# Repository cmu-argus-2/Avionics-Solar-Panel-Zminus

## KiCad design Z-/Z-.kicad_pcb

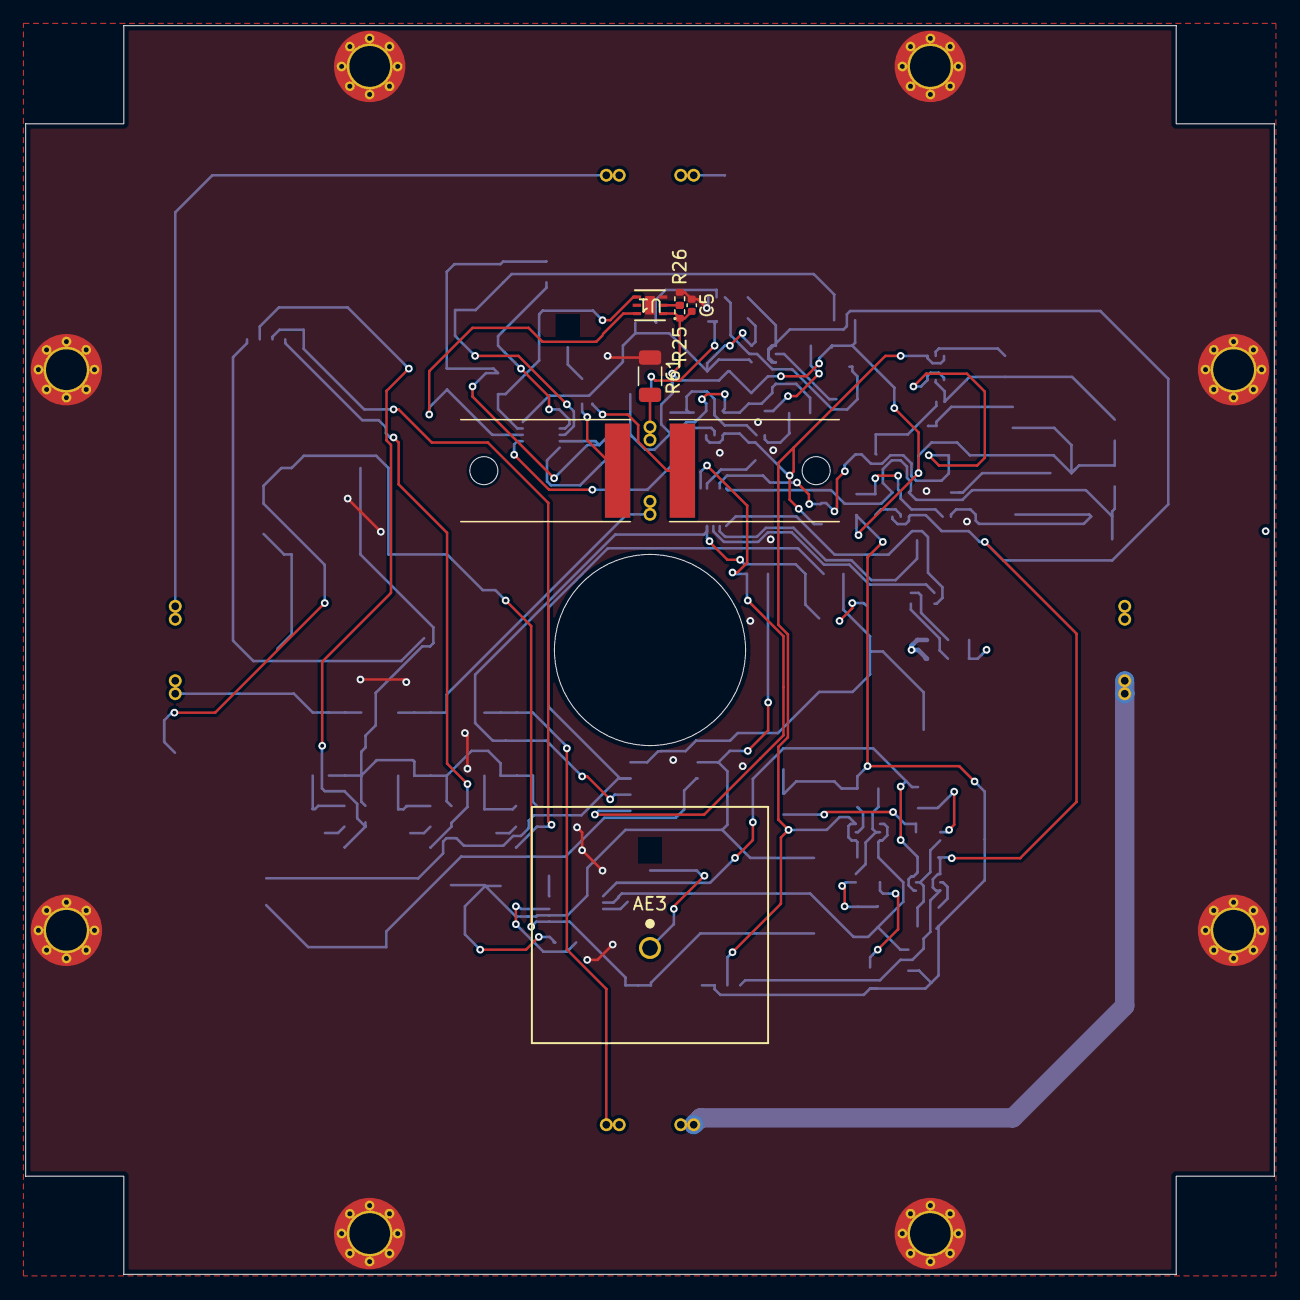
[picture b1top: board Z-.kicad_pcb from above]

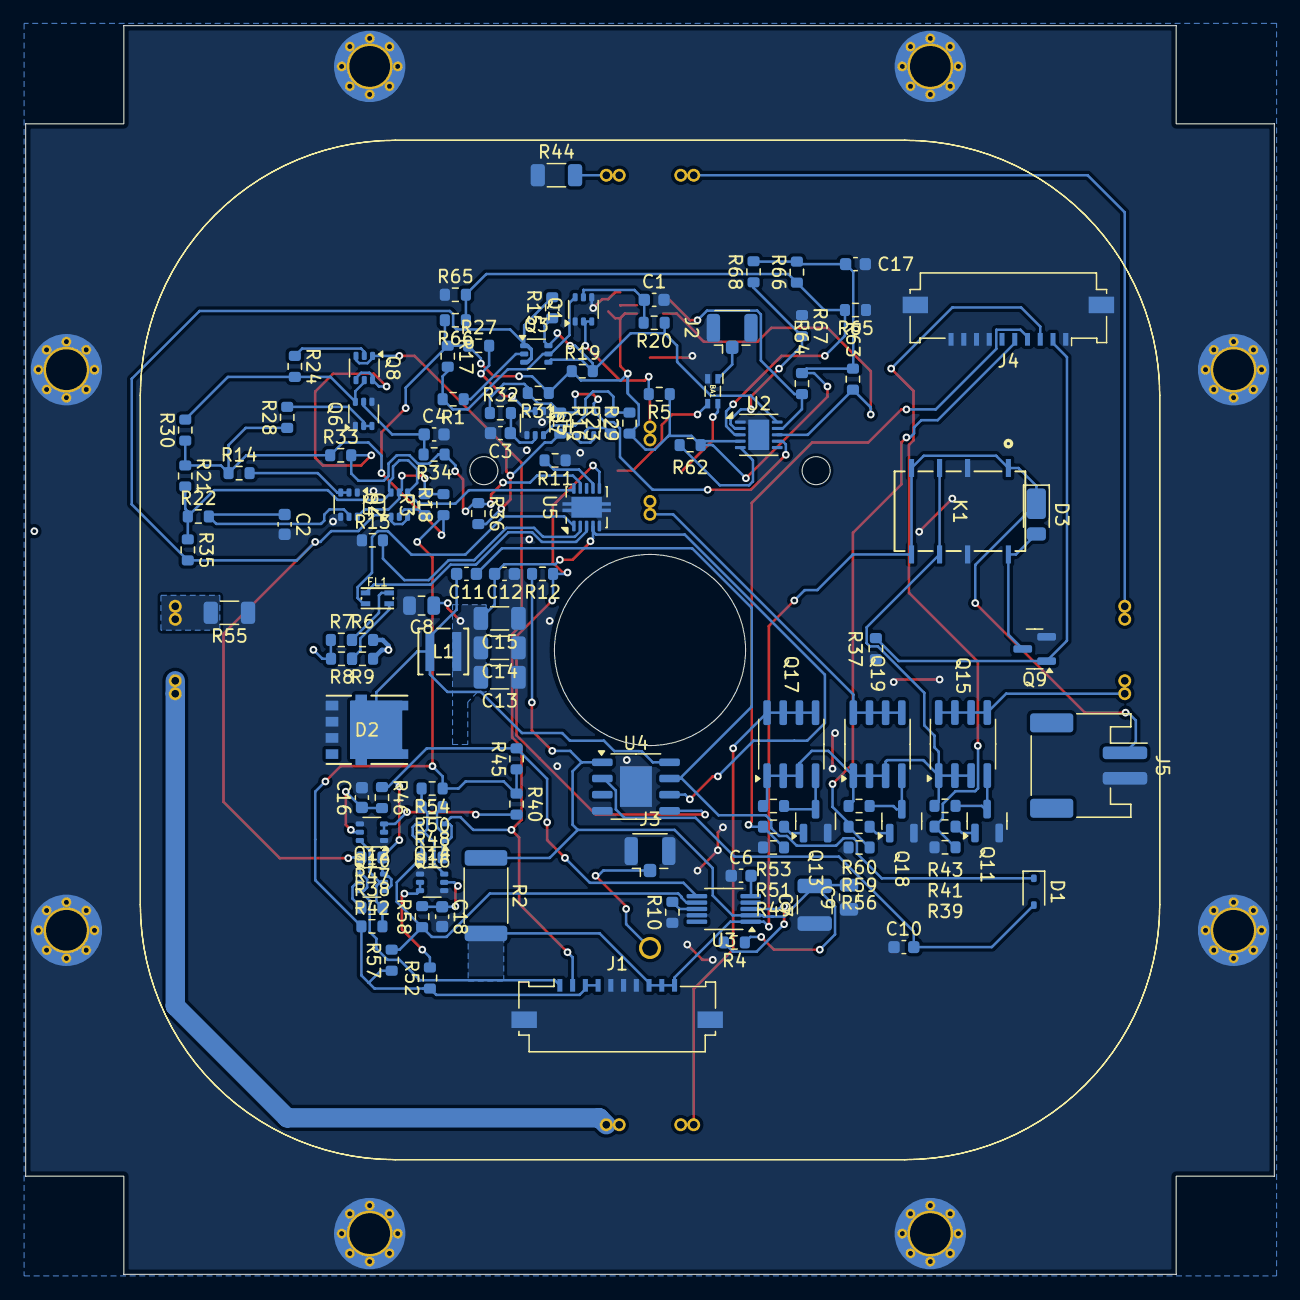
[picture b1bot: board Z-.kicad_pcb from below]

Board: 4 copper layers, 98.0 x 98.0 mm, 140 parts (121 on the bottom side), 81 nets.

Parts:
AE1, AE2: MountingHole_Pad; Antenna Mount
AE3: GPS Antenna; ANT_CGGBP.18.4.A.02_TAL
BA1: ATB2012-50011-T000; ATB2012
C1, C2, C3, C4, C16, C18: 10nF; C_0603_1608Metric
C5: 0.1uF; C_0402_1005Metric
C6: 3.3nF; C_0603_1608Metric
C7: 4.7uF; C_1210_3225Metric
C8: 0.1uF; C_0805_2012Metric
C9: 1uF; C_0805_2012Metric
C10, C11, C12, C17: 0.1uF; C_0603_1608Metric
C13, C14, C15: 10uF; C_1206_3216Metric
D1: BAS16HT1G; D_SOD-323
D2: NRVB440MFS; NRVB440MFSWFT1G
D3: DFLS130L; D_PowerDI-123
FL1: SRF2012
H1, H2, H3, H4, H5, H6, H7, H8: MountingHole_Pad; MountingHole_3.2mm_M3_DIN965_Pad_TopBottom
J1, J4: 200528-0100; Molex_200528-0100_1x10-1MP_P1.00mm_Horizontal
J2, J3: Conn_Coaxial; U.FL_Hirose_U.FL-R-SMT-1_Vertical
J5: Conn_01x02; JST_PH_S2B-PH-SM4-TB_1x02-1MP_P2.00mm_Horizontal
JP1, JP2, JP3, JP4, JP5: BurnWire; Burn-Wire
K1: IM02DGR; RELAY8_SMTGUL_TEC
L1: XGL3520-222; XGL3520
Q1, Q2, Q5, Q6, Q10, Q14: NX3008NBKS; SOT-363_SC-70-6
Q3, Q4, Q7, Q8, Q12, Q16: MBT2222ADW1T1; SOT-363_SC-70-6
Q9: MMBT2222AT; SOT-23
Q11, Q13, Q18: IRLML2803; SOT-23
Q15, Q17, Q19: IRF7404; SOIC-8_3.9x4.9mm_P1.27mm
R1, R3, R23, R24, R38, R50: 680R; R_0603_1608Metric
R2: ?R; R_2512_6332Metric
R4: 1K; R_0603_1608Metric
R5, R14, R27, R28, R40, R43, R52, R53, R60: 100K; R_0603_1608Metric
R6, R7, R8, R9, R10, R11, R13, R65#2: 0R; R_0603_1608Metric
R12, R17, R18, R19, R21, R29, R30, R31, R33, R37, R39, R42, R45, R49, R54, R56, R57, R62, R63, R64: 10K; R_0603_1608Metric
R15, R16, R35, R36, R47, R48, R66#2: DNI (0R); R_0603_1608Metric
R20, R22, R32, R34, R46, R58: 200K; R_0603_1608Metric
R25, R26: 0R; R_0402_1005Metric
R41, R51, R59: 4.7K; R_0603_1608Metric
R44, R55, R61: 1R; R_1206_3216Metric
R65, R66: ?; R_0603_1608Metric
R67: 102K; R_0603_1608Metric
R68: 976K; R_0603_1608Metric
U1: OPT4003DNPRQ1; OPT4003
U2: LTC4316xDD; DFN-10-1EP_3x3mm_P0.5mm_EP1.65x2.38mm
U3: ADM1176-1ARMZ-R7; MSOP-10_3x3mm_P0.5mm
U4: NCV891330PD50R2G; SOIC-8-1EP_3.9x4.9mm_P1.27mm_EP2.514x3.2mm
U5: DRV8830DRC; VSON-10-1EP_3x3mm_P0.5mm_EP1.65x2.4mm

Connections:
3.3V: C5.1, C17.1, J1.3, J1.4, R5.1, R14.1, R17.1, R18.1, R19.1, R21.1, R25.2, R27.1, R28.1, R29.1, R30.1, R31.1, R33.1, R40.1, R42.1, R45.1, R52.1, R54.1, R57.1, R62.2, R63.2, R64.2, R66.2, R66#2.2, R68.2, U1.1 (VDD), U2.4 (V_{CC})
+5V: C8.1, C12.2, C13.2, C14.2, C15.2, L1.2, U4.6 (VOUT), U5.4 (VCC)
/Burn Wires/VBURN1: JP1.1, Q15.5 (Drain), Q15.6 (Drain), Q15.7 (Drain), Q15.8 (Drain)
/Burn Wires/VBURN2: JP2.1, Q17.5 (Drain), Q17.6 (Drain), Q17.7 (Drain), Q17.8 (Drain)
/Burn Wires/VBURN3: JP3.1, Q19.5 (Drain), Q19.6 (Drain), Q19.7 (Drain), Q19.8 (Drain)
/Burn Wires/VBURN_A_IN: K1.3, K1.6, Q15.1 (Source), Q15.2 (Source), Q15.3 (Source), Q17.1 (Source), Q17.2 (Source), Q17.3 (Source), Q19.1 (Source), Q19.2 (Source), Q19.3 (Source), R43.2, R53.2, R60.2
/I2C Devices/SCLOUT: R64.1, U1.4 (SCL), U2.9 (SCLOUT)
/I2C Devices/SDAOUT: R63.1, U1.6 (SDA), U2.8 (SDAOUT)
/coil: R6.2, R7.1, R8.2, R9.1
BURN_EN1: J4.3, R39.1, R41.2
BURN_EN2: J4.4, R49.1, R51.2
BURN_EN3: J4.5, R56.1, R59.2
BURN_RELAY_A: J4.2, Q9.1 (B), R37.1
COIL_N: FL1.4, R8.1, R9.2
COIL_P: FL1.2, R6.1, R7.2
GND: BA1.2 (GND), C1.2, C2.2, C3.2, C4.2, C5.2, C6.1, C7.1, C8.2, C9.1, C10.1, C12.1, C13.1, C14.1, C15.1, C16.2, C17.2, C18.2, D2.2 (A), H1.1, H2.1, H3.1, H4.1, H5.1, H6.1, H7.1, H8.1, J1.5, J1.6, J1.7, J1.MP (MountPin), J2.2 (Ext), J3.2 (Ext), J4.1, J4.7, J4.8, J4.9, J4.10, J4.MP (MountPin), J5.2, K1.2, K1.7, Q1.1 (S2), Q1.4 (S1), Q2.1 (S2), Q2.4 (S1), Q5.1 (S2), Q5.4 (S1), Q6.1 (S2), Q6.4 (S1), Q9.2 (E), Q10.1 (S2), Q10.4 (S1), Q11.2 (S), Q13.2 (S), Q14.1 (S2), Q14.4 (S1), Q18.2 (S), R10.1, R11.1, R13.1, R26.1, R37.2, R39.2, R44.1, R49.2, R55.1, R56.2, R61.1, R65.1, R65#2.1, R67.1, U1.3 (GND), U1.7 (EPAD), U2.1 (GND), U2.11 (EP), U3.4 (GND), U3.9 (A1), U4.4 (GND), U4.9 (GND), U5.5 (GND), U5.11 (EP)
M_FAULT: R12.1, U4.5 (EN), U5.6 (FAULTn)
unnamed: AE1.1, BA1.3
unnamed: AE2.1, BA1.4
unnamed: AE3.1 (A), J3.1 (In)
unnamed: C10.2, D1.2 (A), U4.2 (DRV)
unnamed: C11.1, D1.1 (K), U4.7 (BST)
unnamed: C11.2, D2.1 (K), L1.1, U4.8 (SW)
unnamed: D3.2 (A), K1.8, Q9.3 (C)
unnamed: BA1.1, J2.1 (In)
unnamed: JP1.2, JP4.1
unnamed: JP2.2, JP5.1
unnamed: JP3.2, R61.2
unnamed: JP4.2, R44.2
unnamed: JP5.2, R55.2
unnamed: Q1.6 (D1), Q3.5 (B2), R1.2, R17.2
unnamed: Q1.2 (G2), Q1.3 (D2), R5.2
unnamed: C1.1, Q1.5 (G1), R20.2
unnamed: Q2.6 (D1), Q4.5 (B2), R3.2, R18.2
unnamed: Q2.2 (G2), Q2.3 (D2), R14.2
unnamed: C2.1, Q2.5 (G1), R22.2
unnamed: Q3.2 (B1), R1.1
unnamed: Q4.2 (B1), R3.1
unnamed: Q5.6 (D1), Q7.5 (B2), R23.2, R29.2
unnamed: Q5.2 (G2), Q5.3 (D2), R27.2
unnamed: C3.1, Q5.5 (G1), R32.2
unnamed: Q6.6 (D1), Q8.5 (B2), R24.2, R30.2
unnamed: Q6.2 (G2), Q6.3 (D2), R28.2
unnamed: C4.1, Q6.5 (G1), R34.2
unnamed: Q7.2 (B1), R23.1
unnamed: Q8.2 (B1), R24.1
unnamed: Q10.6 (D1), Q12.5 (B2), R38.2, R42.2
unnamed: Q10.2 (G2), Q10.3 (D2), R40.2
unnamed: C16.1, Q10.5 (G1), R46.2
unnamed: Q11.3 (D), Q15.4 (Gate), R43.1
unnamed: Q11.1 (G), R41.1
unnamed: Q12.2 (B1), R38.1
unnamed: Q13.3 (D), Q17.4 (Gate), R53.1
unnamed: Q13.1 (G), R51.1
unnamed: Q14.6 (D1), Q16.5 (B2), R50.2, R54.2
unnamed: Q14.2 (G2), Q14.3 (D2), R52.2
unnamed: C18.1, Q14.5 (G1), R58.2
unnamed: Q16.2 (B1), R50.1
unnamed: Q18.3 (D), Q19.4 (Gate), R60.1
unnamed: Q18.1 (G), R59.1
unnamed: R25.1, R26.2, U1.2 (ADDR)
unnamed: R62.1, U2.5 (ENABLE)
unnamed: R67.2, R68.1, U2.2 (XORH)
unnamed: R65.2, R65#2.2, R66.1, R66#2.1, U2.3 (XORL)
unnamed: R10.2, U3.8 (A0)
unnamed: R4.2, U3.3 (ON)
unnamed: C6.2, U3.5 (TIMER)
unnamed: R11.2, U5.7 (A0)
unnamed: R13.2, U5.2 (ISENSE)
unnamed: FL1.1, U5.3 (OUT1)
unnamed: FL1.3, U5.1 (OUT2)
SCL: J1.1, Q3.1 (E1), Q3.3 (C2), Q4.1 (E1), Q4.3 (C2), Q12.1 (E1), Q12.3 (C2), R15.2, R35.2, R47.2
SCL_CPWR: Q12.4 (E2), Q12.6 (C1), R45.2, R46.1, R47.1, U3.6 (SCL)
SCL_LS: Q3.4 (E2), Q3.6 (C1), R15.1, R19.2, R20.1, U2.10 (SCLIN)
SCL_M: Q4.4 (E2), Q4.6 (C1), R21.2, R22.1, R35.1, U5.10 (SCL)
SDA: J1.2, Q7.1 (E1), Q7.3 (C2), Q8.1 (E1), Q8.3 (C2), Q16.1 (E1), Q16.3 (C2), R16.2, R36.2, R48.2
SDA_CPWR: Q16.4 (E2), Q16.6 (C1), R48.1, R57.2, R58.1, U3.7 (SDA)
SDA_LS: Q7.4 (E2), Q7.6 (C1), R16.1, R31.2, R32.1, U2.7 (SDAIN)
SDA_M: Q8.4 (E2), Q8.6 (C1), R33.2, R34.1, R36.1, U5.9 (SDA)
VBATT: D3.1 (K), J1.8, J1.9, J1.10, J5.1, K1.1, K1.4, K1.5, R2.2, U3.1 (VCC)
VDRIVE: C7.2, C9.2, R2.1, R4.1, R12.2, U3.2 (SENSE), U4.1 (VIN)

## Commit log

2024-09-30 Prototype for Testing
